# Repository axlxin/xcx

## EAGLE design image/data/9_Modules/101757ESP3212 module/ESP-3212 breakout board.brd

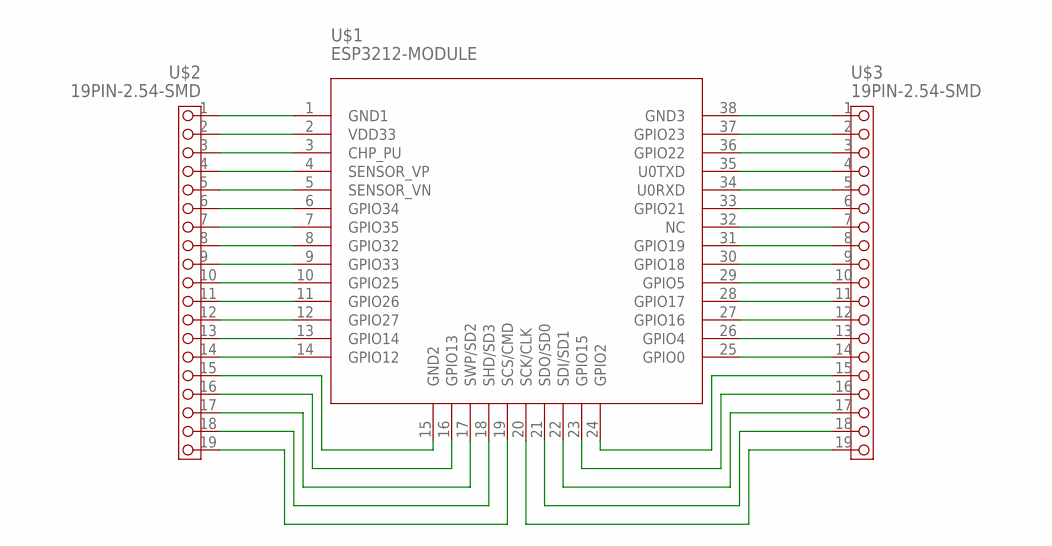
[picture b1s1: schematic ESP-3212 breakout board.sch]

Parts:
U$1: ESP3212-MODULE
U$2, U$3: 19PIN-2.54-SMD

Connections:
GND: U$1.1 (GND1), U$1.15 (GND2), U$1.38 (GND3), U$2.1, U$2.15, U$3.1
unnamed: U$1.2 (VDD33), U$2.2
unnamed: U$1.3 (CHP_PU), U$2.3
unnamed: U$1.4 (SENSOR_VP), U$2.4
unnamed: U$1.5 (SENSOR_VN), U$2.5
unnamed: U$1.6 (GPIO34), U$2.6
unnamed: U$1.7 (GPIO35), U$2.7
unnamed: U$1.8 (GPIO32), U$2.8
unnamed: U$1.9 (GPIO33), U$2.9
unnamed: U$1.10 (GPIO25), U$2.10
unnamed: U$1.11 (GPIO26), U$2.11
unnamed: U$1.12 (GPIO27), U$2.12
unnamed: U$1.13 (GPIO14), U$2.13
unnamed: U$1.14 (GPIO12), U$2.14
unnamed: U$1.16 (GPIO13), U$2.16
unnamed: U$1.17 (SWP/SD2), U$2.17
unnamed: U$1.18 (SHD/SD3), U$2.18
unnamed: U$1.19 (SCS/CMD), U$2.19
unnamed: U$1.37 (GPIO23), U$3.2
unnamed: U$1.36 (GPIO22), U$3.3
unnamed: U$1.35 (U0TXD), U$3.4
unnamed: U$1.34 (U0RXD), U$3.5
unnamed: U$1.33 (GPIO21), U$3.6
unnamed: U$1.32 (NC), U$3.7
unnamed: U$1.31 (GPIO19), U$3.8
unnamed: U$1.30 (GPIO18), U$3.9
unnamed: U$1.29 (GPIO5), U$3.10
unnamed: U$1.28 (GPIO17), U$3.11
unnamed: U$1.27 (GPIO16), U$3.12
unnamed: U$1.26 (GPIO4), U$3.13
unnamed: U$1.25 (GPIO0), U$3.14
unnamed: U$1.24 (GPIO2), U$3.15
unnamed: U$1.23 (GPIO15), U$3.16
unnamed: U$1.22 (SDI/SD1), U$3.17
unnamed: U$1.21 (SDO/SD0), U$3.18
unnamed: U$1.20 (SCK/CLK), U$3.19

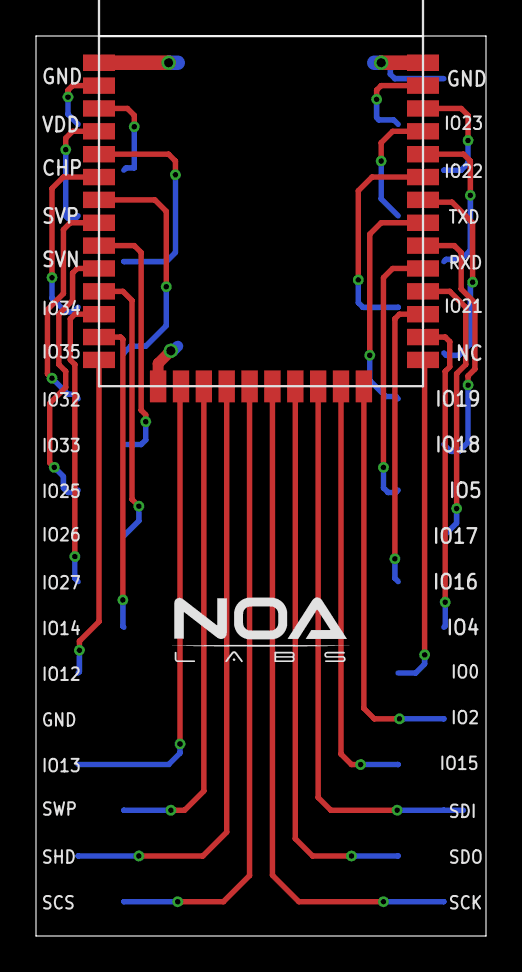
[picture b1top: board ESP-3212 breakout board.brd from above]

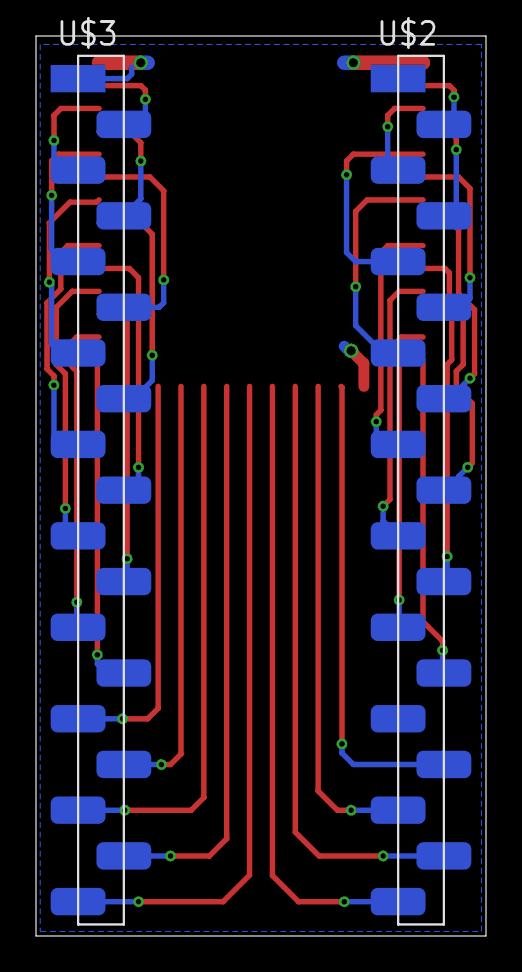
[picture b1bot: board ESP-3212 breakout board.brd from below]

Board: 2 copper layers, 25.0 x 50.0 mm, 3 parts (2 on the bottom side), 36 nets.

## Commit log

2018-05-29 Create ab
2018-09-13 第一次提交
2018-09-13 opencart
